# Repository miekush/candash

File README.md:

# CANDash
STM32 based Controller Area Network Dashboard

Designed by Mike Kushnerik (MKE) in KiCad V5

# License

MKE supports the open source hardware community by sharing hardware design files freely on GitHub!

Please support MKE by purchasing products on [Tindie](https://www.tindie.com/stores/mkengineering/)!

Designed by Mike Kushnerik for MKEngineering

Licensed under [Creative Commons Attribution-ShareAlike CC BY-SA 3.0](http://creativecommons.org/licenses/by-sa/3.0/)

All text above must be included in any redistribution!

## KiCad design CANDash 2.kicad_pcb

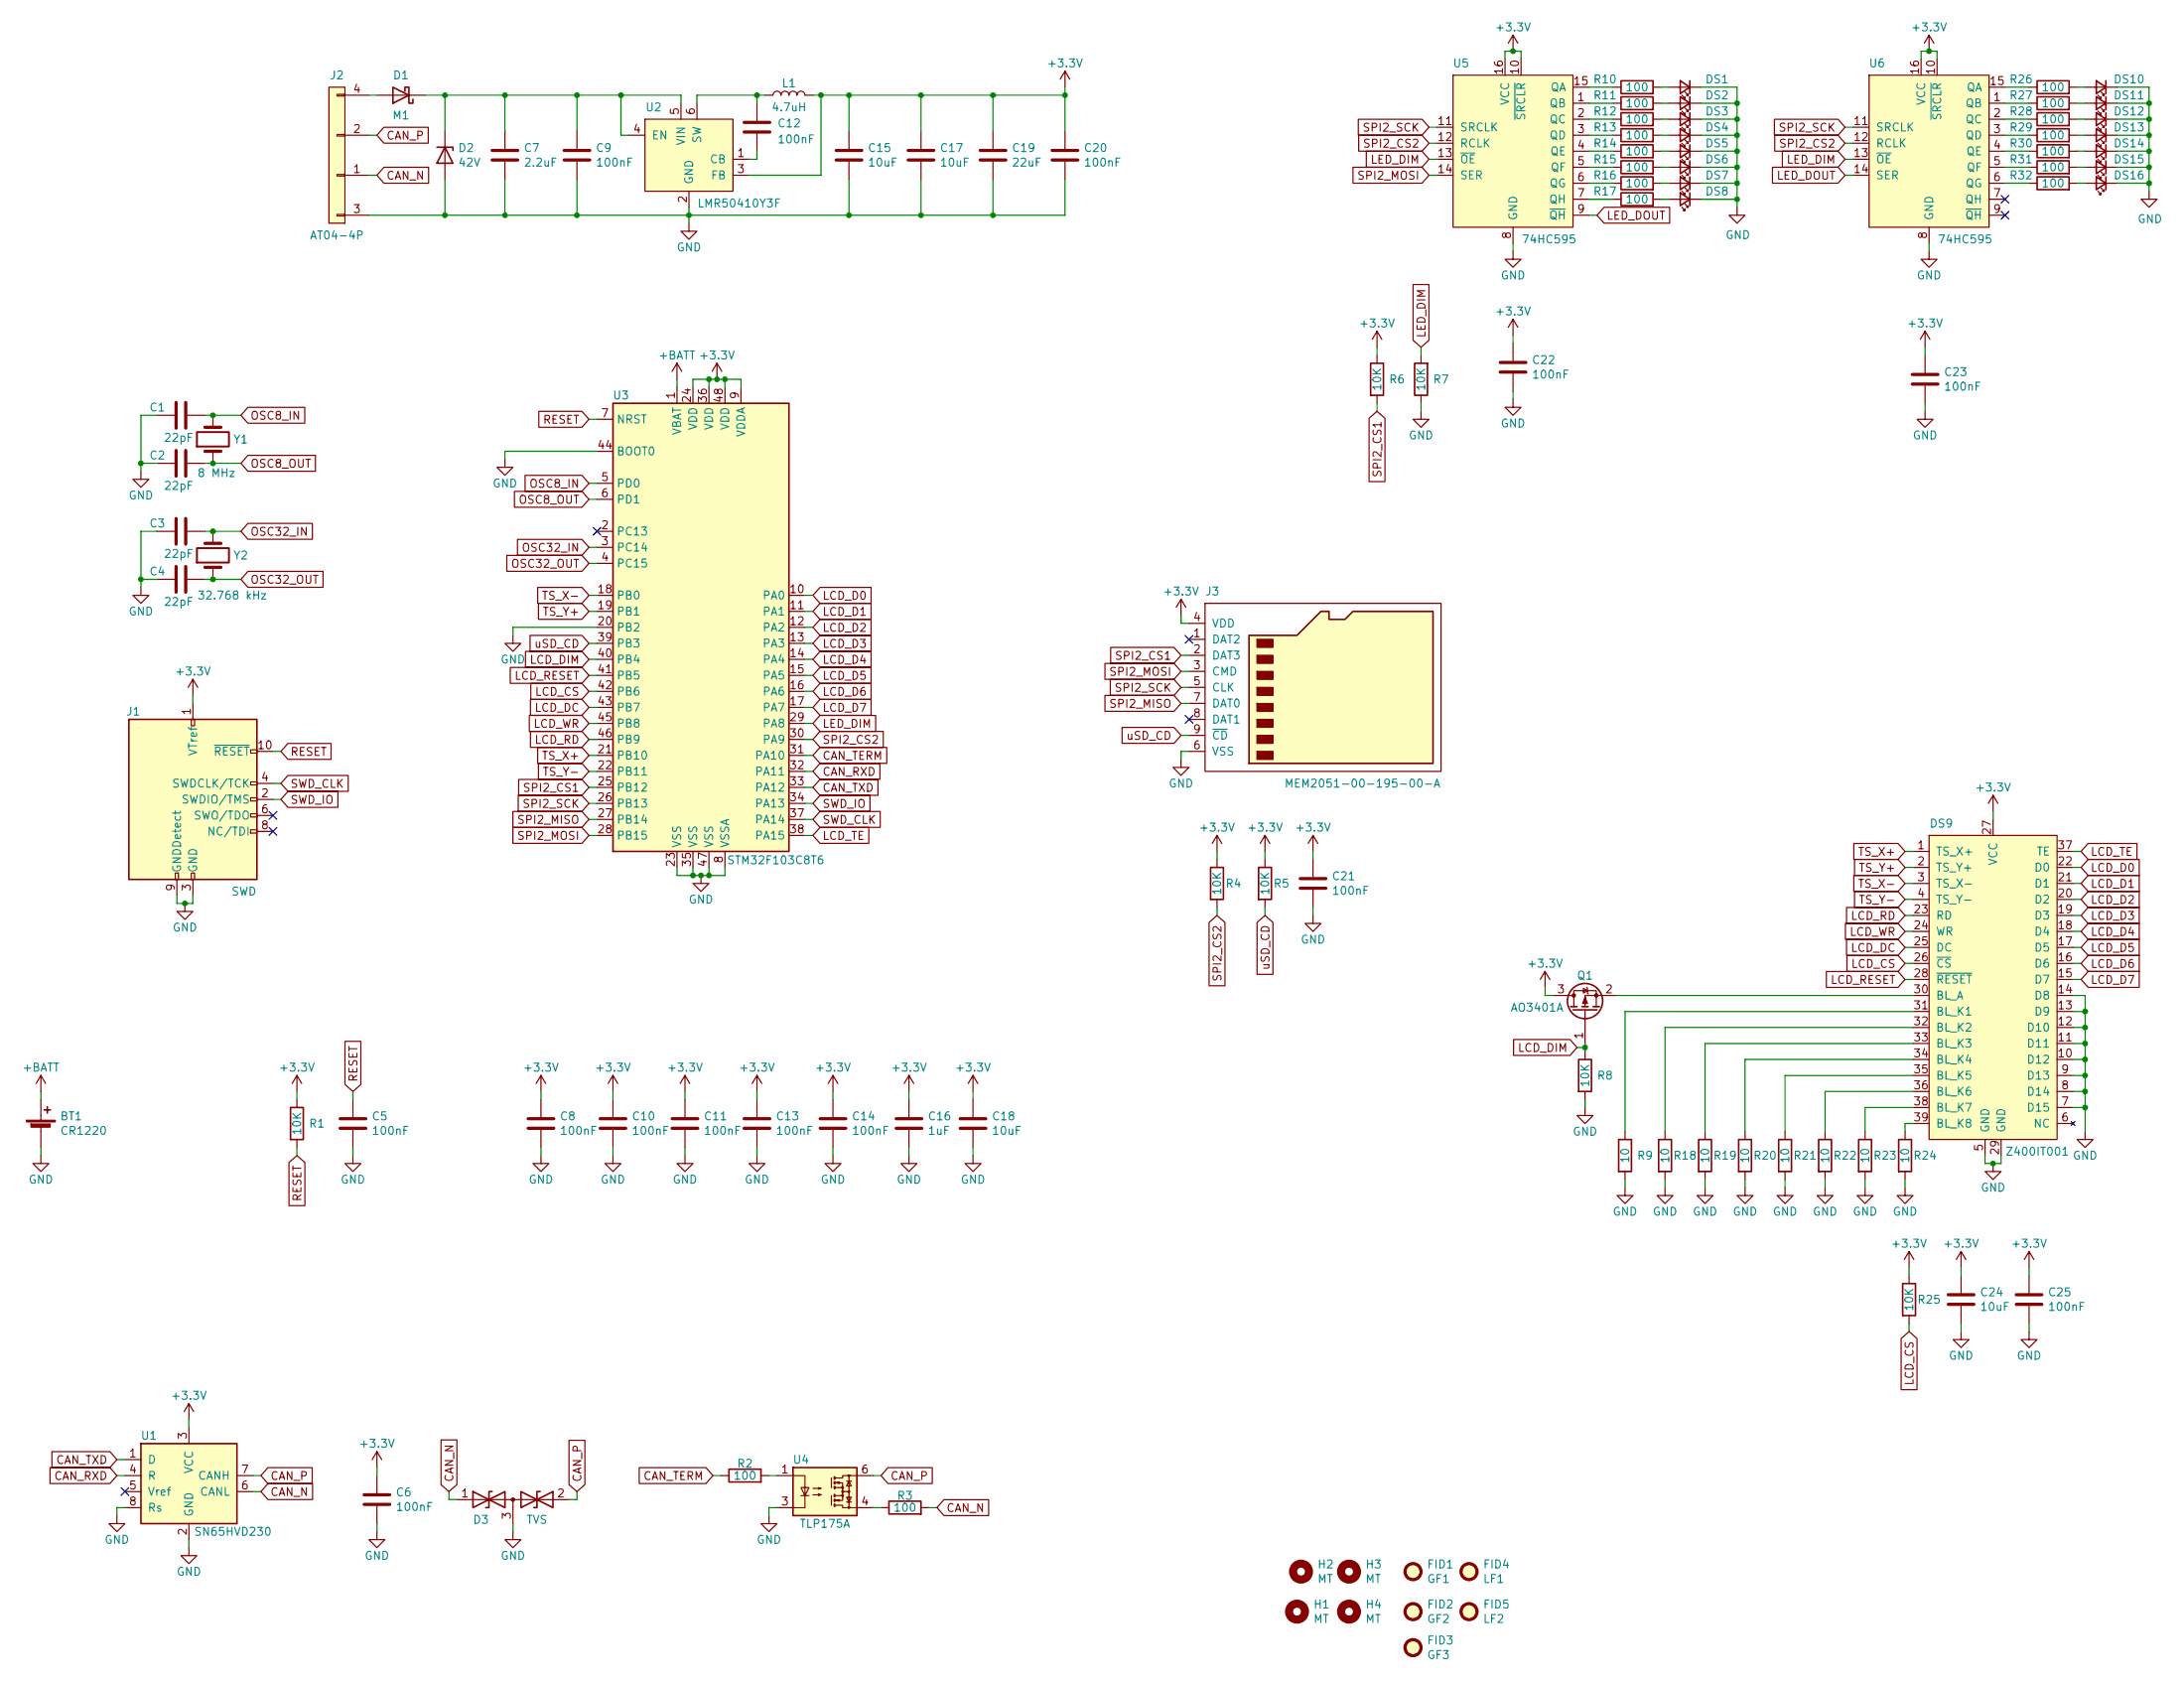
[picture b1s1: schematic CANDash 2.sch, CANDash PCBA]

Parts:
BT1: CR1220; 3000TR
C1, C2, C3, C4: 22pF; C_0603_1608Metric; LCSC C1653
C5, C6, C8, C9, C10, C11, C12, C13, C14, C20, C21, C22, C23, C25: 100nF; C_0603_1608Metric; LCSC C14663
C7: 2.2uF; C_1206_3216Metric; LCSC C13585
C15, C17, C18, C24: 10uF; C_0805_2012Metric; LCSC C15850
C16: 1uF; C_0603_1608Metric; LCSC C15849
C19: 22uF; C_1206_3216Metric; LCSC C15850
D1: M1; D_SMA
D2: 42V; D_SMB
D3: TVS; SOT-23; LCSC C343993
DS1, DS2, DS3, DS4, DS5, DS6, DS7, DS8, DS10, DS11, DS12, DS13, DS14, DS15, DS16: LED_Small; LED_D3.0mm
DS9: Z400IT001
FID1: GF1; Fiducial_1mm_Mask3mm
FID2: GF2; Fiducial_1mm_Mask3mm
FID3: GF3; Fiducial_1mm_Mask3mm
FID4: LF1; Fiducial_0.5mm_Mask1mm
FID5: LF2; Fiducial_0.5mm_Mask1mm
H1, H2, H3, H4: MT; MountingHole_3.2mm_M3
J1: SWD; PinHeader_2x05_P2.54mm_Vertical
J2: AT04-4P; AT04-4P-BM03
J3: MEM2051-00-195-00-A
L1: 4.7uH; IFSC1515AHER4R7M01
Q1: AO3401A; SOT-23; LCSC C15127
R1, R4, R5, R6, R7, R8, R25: 10K; R_0603_1608Metric; LCSC C25804
R2: 100; R_0603_1608Metric; LCSC C21190
R3, R10, R11, R12, R13, R14, R15, R16, R17, R26, R27, R28, R29, R30, R31, R32: 100; R_0603_1608Metric; LCSC C22775
R9, R18, R19, R20, R21, R22, R23, R24: 10; R_0603_1608Metric; LCSC C22859
U1: SN65HVD230; SOIC-8_3.9x4.9mm_P1.27mm; LCSC C12084
U2: LMR50410Y3F; SOT-23-6
U3: STM32F103C8T6; LQFP-48_7x7mm_P0.5mm; LCSC C8734
U4: TLP175A; MFSOP6-4_4.4x3.6mm_P1.27mm; LCSC C141522
U5, U6: 74HC595; SOIC-16_3.9x9.9mm_P1.27mm
Y1: 8 MHz; Crystal_SMD_5032-2Pin_5.0x3.2mm; LCSC C115962
Y2: 32.768 kHz; Crystal_SMD_3215-2Pin_3.2x1.5mm; LCSC C115962

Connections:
+3V3: C6.1, C8.1, C10.1, C11.1, C13.1, C14.1, C15.1, C16.1, C17.1, C18.1, C19.1, C20.1, C21.1, C22.1, C23.1, C24.1, C25.1, DS9.27 (VCC), J1.1 (VTref), J3.4 (VDD), L1.2, Q1.3 (D), R1.1, R4.1, R5.1, R6.1, R25.1, U1.3 (VCC), U2.3 (FB), U3.9 (VDDA), U3.24 (VDD), U3.36 (VDD), U3.48 (VDD), U5.10 (~SRCLR), U5.16 (VCC), U6.10 (~SRCLR), U6.16 (VCC)
+BATT: BT1.1 (+), U3.1 (VBAT)
CAN_N: D3.1 (A1), J2.1, R3.2, U1.6 (CANL)
CAN_P: D3.2 (A2), J2.2, U1.7 (CANH), U4.6
CAN_RXD: U1.4 (R), U3.32 (PA11)
CAN_TERM: R2.1, U3.31 (PA10)
CAN_TXD: U1.1 (D), U3.33 (PA12)
GND: BT1.2 (-), C1.2, C2.2, C3.2, C4.2, C5.2, C6.2, C7.2, C8.2, C9.2, C10.2, C11.2, C13.2, C14.2, C15.2, C16.2, C17.2, C18.2, C19.2, C20.2, C21.2, C22.2, C23.2, C24.2, C25.2, D2.2 (A), D3.3 (common), DS1.1 (K), DS2.1 (K), DS3.1 (K), DS4.1 (K), DS5.1 (K), DS6.1 (K), DS7.1 (K), DS8.1 (K), DS9.5 (GND), DS9.7 (D15), DS9.8 (D14), DS9.9 (D13), DS9.10 (D12), DS9.11 (D11), DS9.12 (D10), DS9.13 (D9), DS9.14 (D8), DS9.29 (GND), DS10.1 (K), DS11.1 (K), DS12.1 (K), DS13.1 (K), DS14.1 (K), DS15.1 (K), DS16.1 (K), J1.3 (GND), J1.5 (GND), J1.9 (GNDDetect), J2.3, J3.6 (VSS), R7.1, R8.2, R9.2, R18.2, R19.2, R20.2, R21.2, R22.2, R23.2, R24.2, U1.2 (GND), U1.8 (Rs), U2.2 (GND), U3.8 (VSSA), U3.20 (PB2), U3.23 (VSS), U3.35 (VSS), U3.44 (BOOT0), U3.47 (VSS), U4.3, U5.8 (GND), U6.8 (GND)
LCD_CS: DS9.26 (~CS), R25.2, U3.42 (PB6)
LCD_D0: DS9.22 (D0), U3.10 (PA0)
LCD_D1: DS9.21 (D1), U3.11 (PA1)
LCD_D2: DS9.20 (D2), U3.12 (PA2)
LCD_D3: DS9.19 (D3), U3.13 (PA3)
LCD_D4: DS9.18 (D4), U3.14 (PA4)
LCD_D5: DS9.17 (D5), U3.15 (PA5)
LCD_D6: DS9.16 (D6), U3.16 (PA6)
LCD_D7: DS9.15 (D7), U3.17 (PA7)
LCD_DC: DS9.25 (DC), U3.43 (PB7)
LCD_DIM: Q1.1 (G), R8.1, U3.40 (PB4)
LCD_RD: DS9.23 (RD), U3.46 (PB9)
LCD_RESET: DS9.28 (~RESET), U3.41 (PB5)
LCD_TE: DS9.37 (TE), U3.38 (PA15)
LCD_WR: DS9.24 (WR), U3.45 (PB8)
LED_DIM: R7.2, U3.29 (PA8), U5.13 (~OE), U6.13 (~OE)
LED_DOUT: U5.9 (~QH), U6.14 (SER)
unnamed: C7.1, C9.1, D1.1 (K), D2.1 (K), U2.4 (EN), U2.5 (VIN)
unnamed: C12.1, L1.1, U2.6 (SW)
unnamed: C12.2, U2.1 (CB)
unnamed: D1.2 (A), J2.4
unnamed: DS1.2 (A), R10.2
unnamed: DS2.2 (A), R11.2
unnamed: DS3.2 (A), R12.2
unnamed: DS4.2 (A), R13.2
unnamed: DS5.2 (A), R14.2
unnamed: DS6.2 (A), R15.2
unnamed: DS7.2 (A), R16.2
unnamed: DS8.2 (A), R17.2
unnamed: DS9.30 (BL_A), Q1.2 (S)
unnamed: DS9.31 (BL_K1), R9.1
unnamed: DS9.32 (BL_K2), R18.1
unnamed: DS9.33 (BL_K3), R19.1
unnamed: DS9.34 (BL_K4), R20.1
unnamed: DS9.35 (BL_K5), R21.1
unnamed: DS9.36 (BL_K6), R22.1
unnamed: DS9.38 (BL_K7), R23.1
unnamed: DS9.39 (BL_K8), R24.1
unnamed: DS10.2 (A), R26.2
unnamed: DS11.2 (A), R27.2
unnamed: DS12.2 (A), R28.2
unnamed: DS13.2 (A), R29.2
unnamed: DS14.2 (A), R30.2
unnamed: DS15.2 (A), R31.2
unnamed: DS16.2 (A), R32.2
unnamed: R2.2, U4.1
unnamed: R3.1, U4.4
unnamed: R10.1, U5.15 (QA)
unnamed: R11.1, U5.1 (QB)
unnamed: R12.1, U5.2 (QC)
unnamed: R13.1, U5.3 (QD)
unnamed: R14.1, U5.4 (QE)
unnamed: R15.1, U5.5 (QF)
unnamed: R16.1, U5.6 (QG)
unnamed: R17.1, U5.7 (QH)
unnamed: R26.1, U6.15 (QA)
unnamed: R27.1, U6.1 (QB)
unnamed: R28.1, U6.2 (QC)
unnamed: R29.1, U6.3 (QD)
unnamed: R30.1, U6.4 (QE)
unnamed: R31.1, U6.5 (QF)
unnamed: R32.1, U6.6 (QG)
OSC8_IN: C1.1, U3.5 (PD0), Y1.2
OSC8_OUT: C2.1, U3.6 (PD1), Y1.1
OSC32_IN: C3.1, U3.3 (PC14), Y2.2
OSC32_OUT: C4.1, U3.4 (PC15), Y2.1
RESET: C5.1, J1.10 (~RESET~), R1.2, U3.7 (NRST)
SPI2_CS1: J3.2 (DAT3), R6.2, U3.25 (PB12)
SPI2_CS2: R4.2, U3.30 (PA9), U5.12 (RCLK), U6.12 (RCLK)
SPI2_MISO: J3.7 (DAT0), U3.27 (PB14)
SPI2_MOSI: J3.3 (CMD), U3.28 (PB15), U5.14 (SER)
SPI2_SCK: J3.5 (CLK), U3.26 (PB13), U5.11 (SRCLK), U6.11 (SRCLK)
SWD_CLK: J1.4 (SWDCLK/TCK), U3.37 (PA14)
SWD_IO: J1.2 (SWDIO/TMS), U3.34 (PA13)
TS_X+: DS9.1 (TS_X+), U3.21 (PB10)
TS_X-: DS9.3 (TS_X-), U3.18 (PB0)
TS_Y+: DS9.2 (TS_Y+), U3.19 (PB1)
TS_Y-: DS9.4 (TS_Y-), U3.22 (PB11)
uSD_CD: J3.9 (~CD), R5.2, U3.39 (PB3)

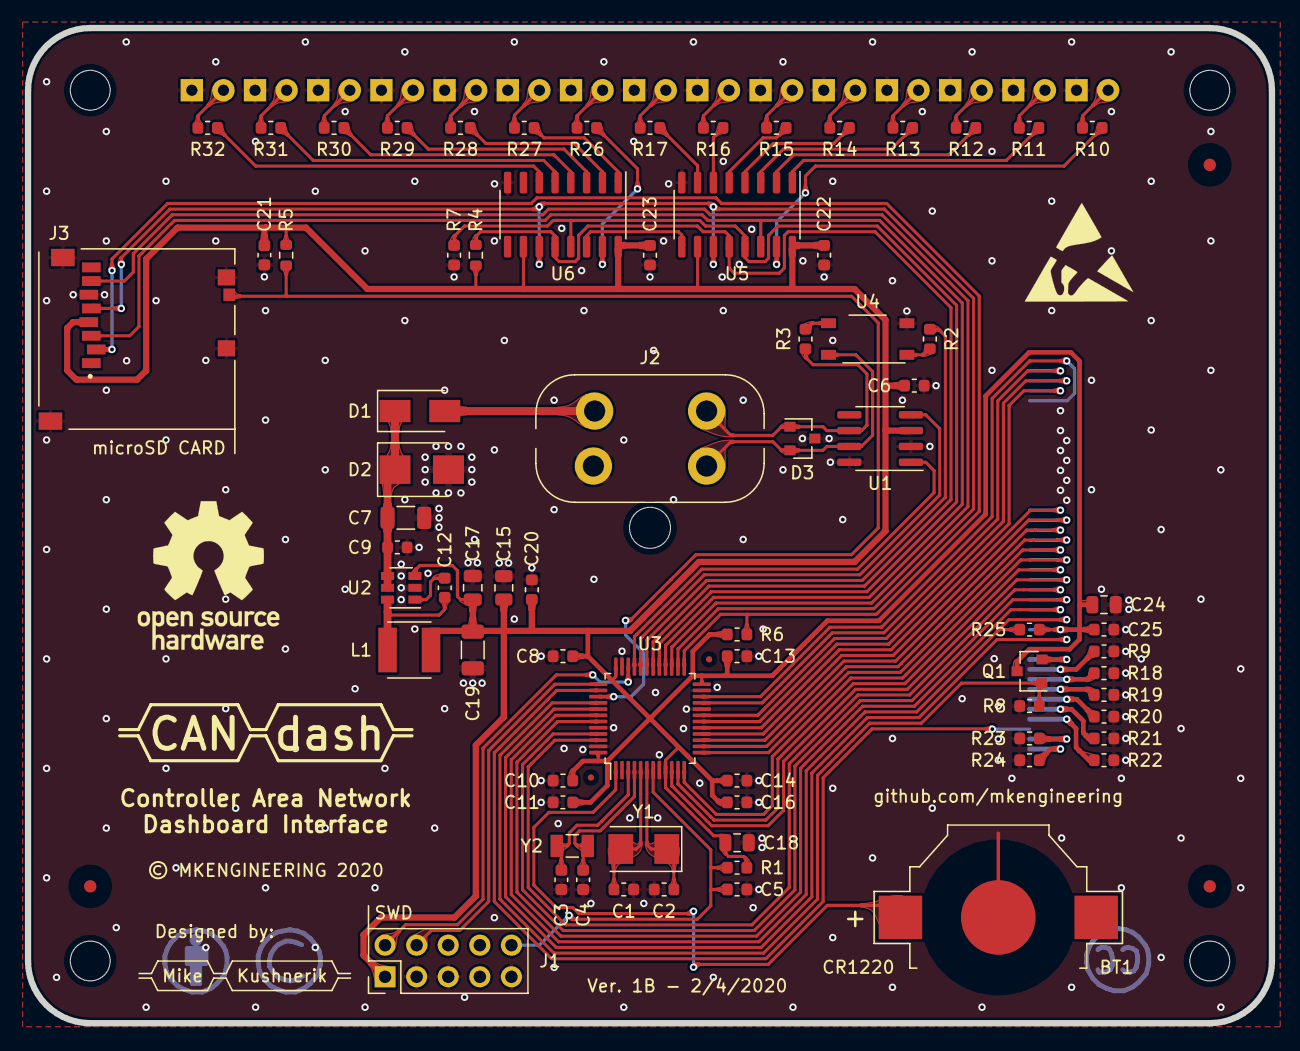
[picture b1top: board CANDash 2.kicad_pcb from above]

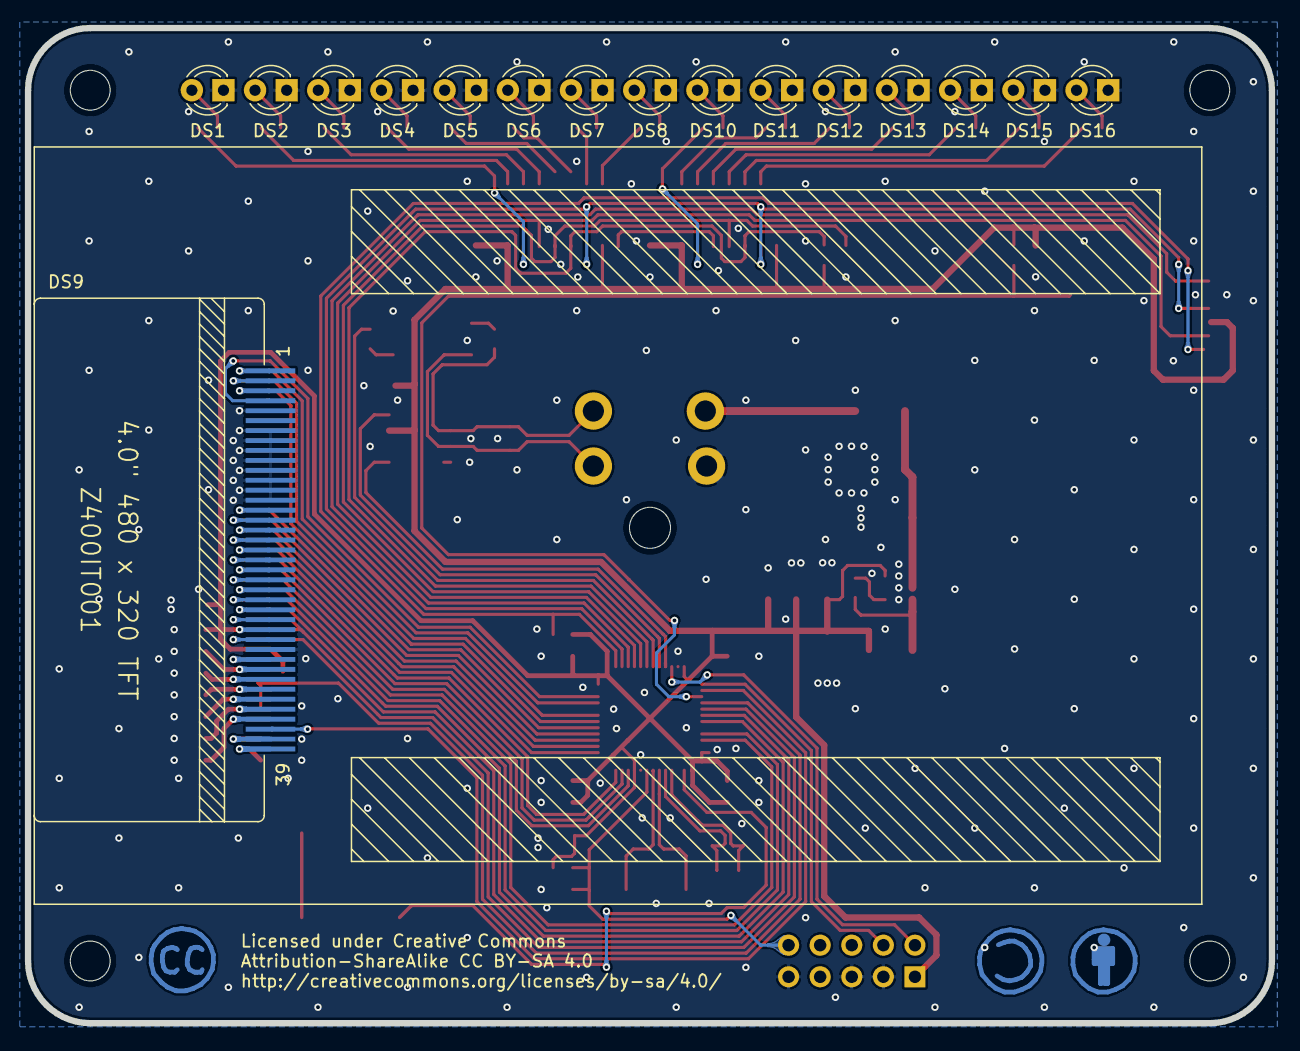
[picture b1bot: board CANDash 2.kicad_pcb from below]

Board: 2 copper layers, 100.0 x 80.0 mm, 99 parts (16 on the bottom side), 87 nets.

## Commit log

2019-12-26 Add 12-24-2019 REV A Gerber and Drill Files
    Latest Gerber and Drill Files for the CANDash main PCB.
    Fixes:
    -Added 150K pull ups onto the LP55231 INT and EN pins
    -Added 150K pull down onto the LP55231 TRIG pins
    -Added 100K pull up to uSD card CS pin
    -Replaced VHN5019 driver IC with two, MJD122 NPN Darlington Transistors
2019-12-26 Delete CANDash_Drill_12_24_19.Cam
    -moved to PCB Files
2019-12-26 Delete CANDash_Gerber_12_24_19.Cam
    -moved to PCB Files
2019-12-26 Create PCB Fabrication Files
2019-12-26 Create new
2019-12-26 Add 12-24-2019 REV 1A Gerber and Drill Files
    Latest Gerber and Drill Files for the CANDash main PCB.
    Fixes:
    -Added 150K pull ups onto the LP55231 INT and EN pins
    -Added 150K pull down onto the LP55231 TRIG pins
    -Added 100K pull up to uSD card CS pin
    -Replaced VHN5019 driver IC with two, MJD122 NPN Darlington Transistors
2019-12-26 Add Rev. 1A PCB CAD Photos
    CAD Renderings of the Rev. 1A CANDash PCB
2019-12-26 Add Gerber Photos
    Gerber Photos of the Rev. 1A CANDash PCB
2021-05-28 Initial Upload

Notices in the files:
CANDash 2.kicad_pcb:
Attribution-ShareAlike CC BY-SA 4.0
http://creativecommons.org/licenses/by-sa/4.0
© MKENGINEERING 2020
